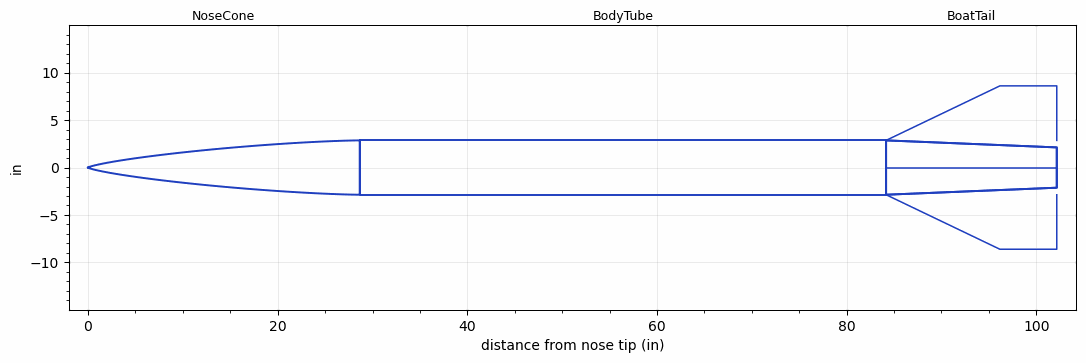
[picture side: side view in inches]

<RASAeroDocument>
 <FileVersion>2</FileVersion>
 <RocketDesign>
  <NoseCone>
   <Length>28.65</Length>
   <Diameter>5.73</Diameter>
   <Shape>Von Karman Ogive</Shape>
   <Location>0</Location>
  </NoseCone>
  <BodyTube>
   <Length>55.51</Length>
   <Diameter>5.73</Diameter>
   <LaunchLugDiameter>0.5</LaunchLugDiameter>
   <LaunchLugLength>1</LaunchLugLength>
   <Location>28.65</Location>
   <BoattailLength>18</BoattailLength>
   <BoattailRearDiameter>4.25</BoattailRearDiameter>
   <Overhang>18</Overhang>
   <Fin>
    <Count>4</Count>
    <Chord>18</Chord>
    <Span>5.75</Span>
    <SweepDistance>12</SweepDistance>
    <TipChord>6</TipChord>
    <Thickness>0.25</Thickness>
    <Location>0</Location>
    <AirfoilSection>Hexagonal</AirfoilSection>
    <FX1>1</FX1>
    <FX3>1</FX3>
   </Fin>
  </BodyTube>
  <BoatTail>
   <Length>18</Length>
   <Diameter>5.73</Diameter>
   <RearDiameter>4.25</RearDiameter>
   <Location>84.16</Location>
  </BoatTail>
  <Surface>Smooth Paint</Surface>
  <ModifiedBarrowman>True</ModifiedBarrowman>
  <Turbulence>False</Turbulence>
  <UseBooster1>False</UseBooster1>
  <UseBooster2>False</UseBooster2>
 </RocketDesign>
 <LaunchSite>
  <Altitude>1214</Altitude>
  <Pressure>30.18</Pressure>
  <RodAngle>6</RodAngle>
  <RodLength>15</RodLength>
  <Temperature>59</Temperature>
  <WindSpeed>9.32</WindSpeed>
 </LaunchSite>
 <Recovery>
  <Altitude1>1000</Altitude1>
  <Altitude2>1500</Altitude2>
  <DeviceType1>Parachute</DeviceType1>
  <DeviceType2>Parachute</DeviceType2>
  <Event1>True</Event1>
  <Event2>True</Event2>
  <Size1>28.01</Size1>
  <Size2>72</Size2>
  <EventType1>Apogee</EventType1>
  <EventType2>Altitude</EventType2>
  <CD1>1.5</CD1>
  <CD2>2.2</CD2>
 </Recovery>
 <SimulationList>
  <Simulation>
   <SustainerEngine>O3400-IM-P  (CTI)</SustainerEngine>
   <SustainerLaunchWt>66.33</SustainerLaunchWt>
   <SustainerNozzleDiameter>2.7</SustainerNozzleDiameter>
   <SustainerCG>64.37</SustainerCG>
   <SustainerIgnitionDelay>0</SustainerIgnitionDelay>
   <Booster1SeparationDelay>0</Booster1SeparationDelay>
   <Booster1IgnitionDelay>0</Booster1IgnitionDelay>
   <IncludeBooster1>False</IncludeBooster1>
   <Booster2Delay>0</Booster2Delay>
   <IncludeBooster2>False</IncludeBooster2>
   <TimetoApogee>39.23942</TimetoApogee>
   <MaxAltitude>30845.14</MaxAltitude>
   <MaxVelocity>2141.53</MaxVelocity>
  </Simulation>
 </SimulationList>
</RASAeroDocument>
